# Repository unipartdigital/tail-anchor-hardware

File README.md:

# tail-anchor-hardware

Standalone anchor for tail

See https://github.com/unipartdigital/tail for more details

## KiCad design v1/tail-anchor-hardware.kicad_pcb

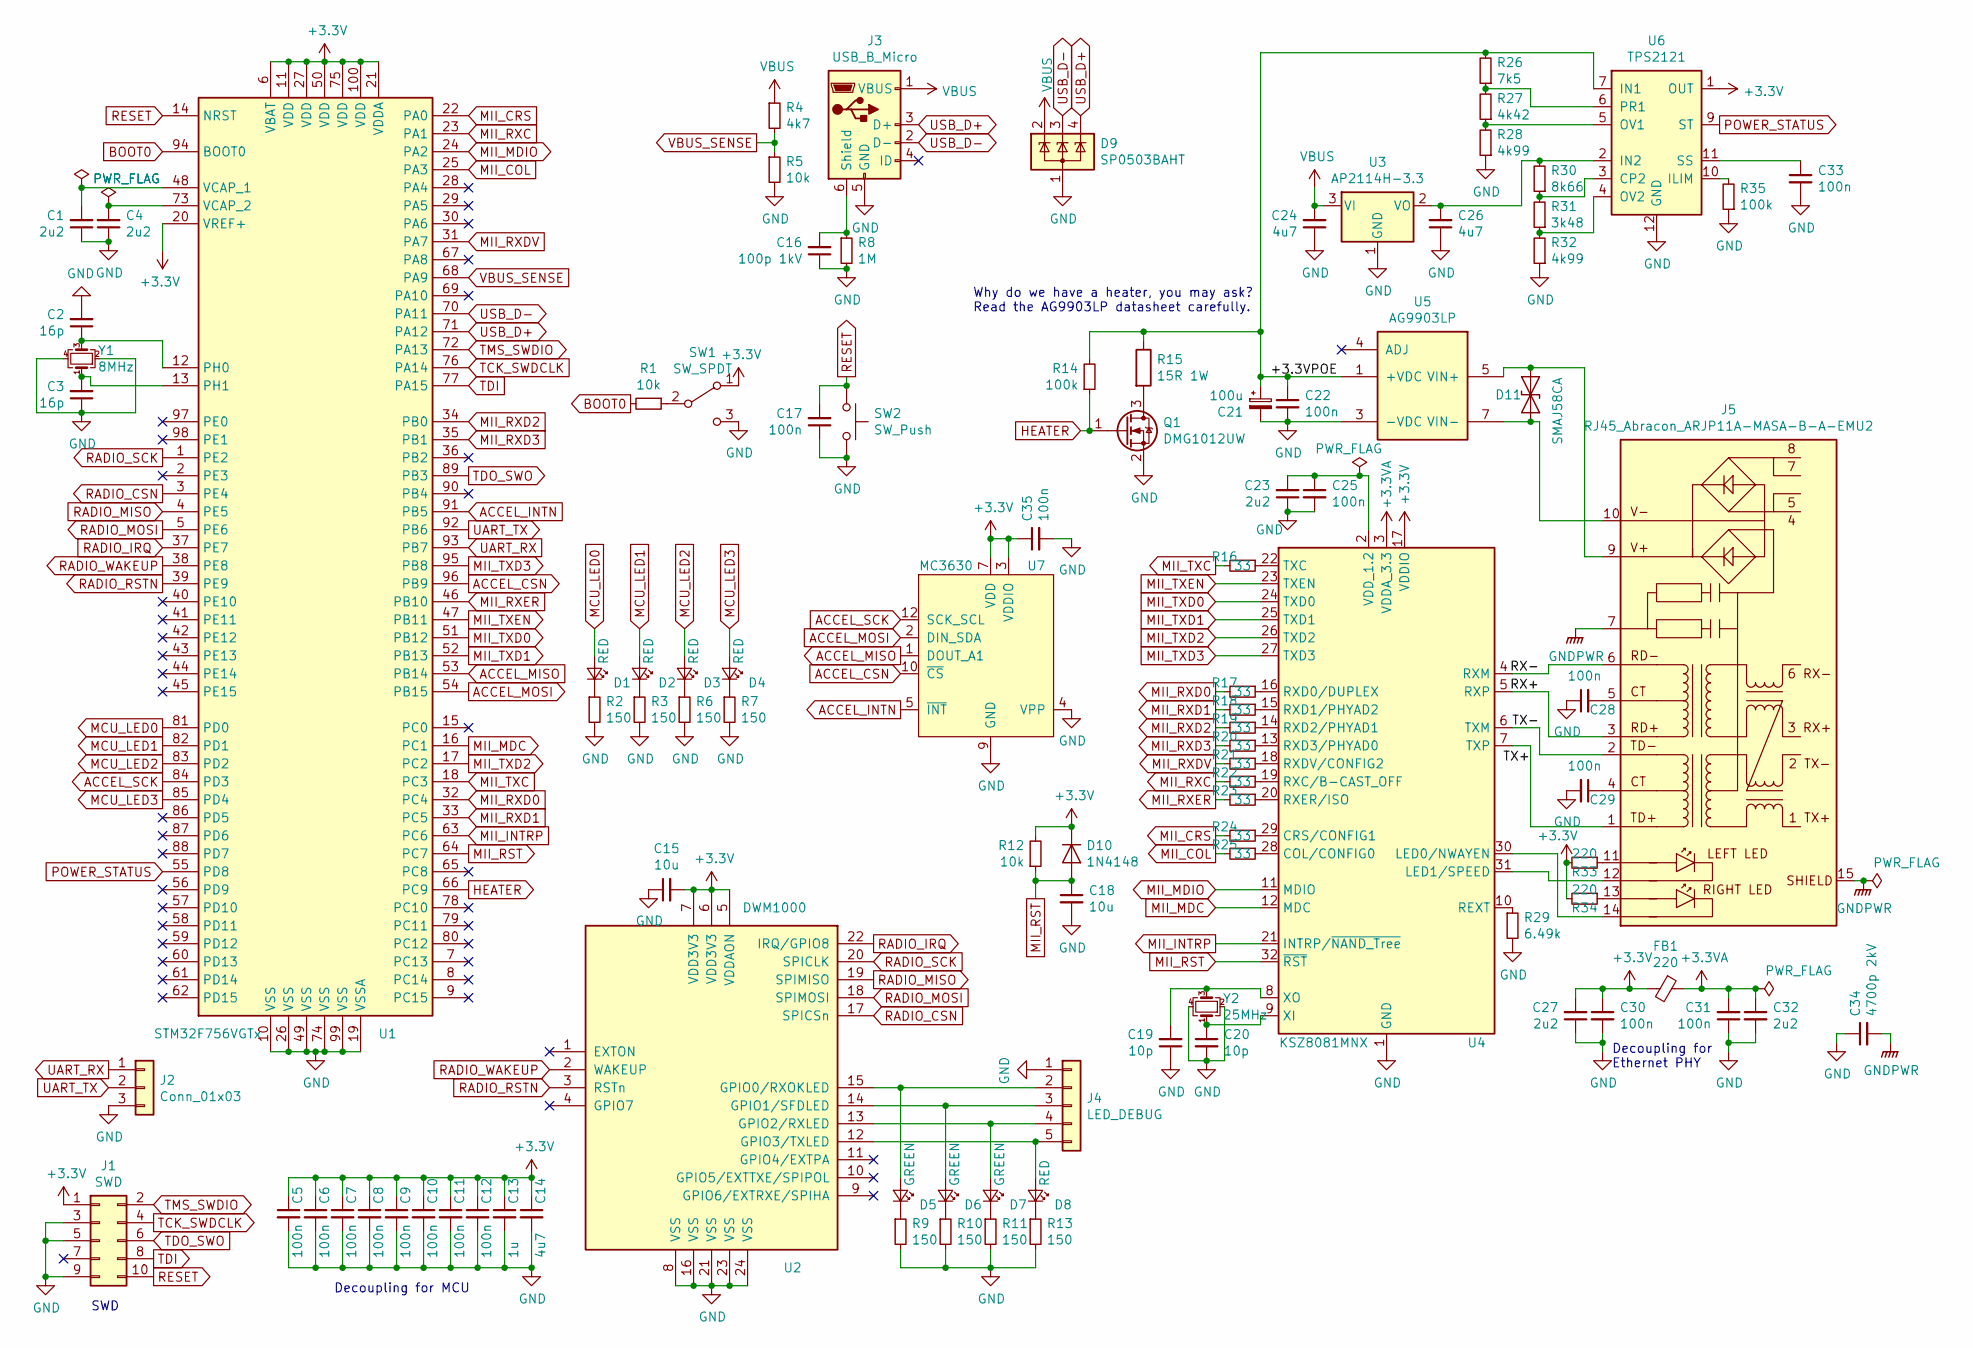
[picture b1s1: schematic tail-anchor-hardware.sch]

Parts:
C1, C4, C23, C27, C32: 2u2; C_0402_1005Metric; MPN GRM155R60J225ME95D
C2, C3: 16p; C_0402_1005Metric; MPN GJM1555C1H160GB01D
C5, C6, C7, C8, C9, C10, C11, C12, C17, C22, C25, C28, C29, C30, C31, C33, C35: 100n; C_0402_1005Metric; MPN MC0402X104K6R3CT
C13: 1u; C_0402_1005Metric; MPN CL05A105KQ5NNNC
C14, C24, C26: 4u7; C_0402_1005Metric; MPN GRM155R60G475ME87D
C15, C18: 10u; C_0402_1005Metric; MPN GRM155R60J106ME44D
C16: 100p 1kV; C_1206_3216Metric; MPN C1206C101JDGACAUTO
C19, C20: 10p; C_0402_1005Metric; MPN MCMT15N100F100CT
C21: 100u; C_Elec_5x5.8; MPN VZT101M1CTR-0506
C34: 4700p 2kV; C_1812_4532Metric; MPN C1812C472KGRACTU
D1, D2, D3, D4, D8: RED; LED_0603_1608Metric; MPN KP-1608SURCK
D5, D6, D7: GREEN; LED_0603_1608Metric; MPN KP-1608CGCK
D9: SP0503BAHT; SOT-143; MPN SP0503BAHTG
D10: 1N4148; D_SOD-123; MPN 1N4148W+
D11: SMAJ58CA; D_SMA; MPN SMAJ58CA
FB1: 220; L_0402_1005Metric; MPN BLM15AG221SN1D
J1: SWD; PinHeader_2x05_P1.27mm_Vertical_SMD; MPN FTSH-105-01-L-DV
J2: Conn_01x03; PinHeader_1x03_P2.54mm_Horizontal; MPN MC34747
J3: USB_B_Micro; USB_Micro-B_Molex_47346-0001; MPN 47346-0001
J4: LED_DEBUG; PinHeader_1x05_P2.54mm_Vertical; MPN 2211S-05G
J5: RJ45_Abracon_ARJP11A-MASA-B-A-EMU2; RJ45_Abracon_ARJP11A-MA_Horizontal; MPN ARJP11A-MASA-B-A-EMU2
Q1: DMG1012UW; SOT-323_SC-70; MPN DMG1012UW
R1, R5, R12: 10k; R_0402_1005Metric; MPN MCWR04X1002FTL
R2, R3, R6, R7, R9, R10, R11, R13: 150; R_0402_1005Metric; MPN MCWR04X1500FTL
R4: 4k7; R_0402_1005Metric; MPN MCWR04X4701FTL
R8: 1M; R_2010_5025Metric; MPN MCHVR0AJTEU1004
R14, R35: 100k; R_0402_1005Metric; MPN MCWR04X1003FTL
R15: 15R 1W; R_MELF_MMB-0207; MPN SMA-A0207FTDT15R
R16, R17, R18, R19, R20, R21, R22, R23, R24, R25: 33; R_0402_1005Metric; MPN CRG0402F33R
R26: 7k5; R_0402_1005Metric; MPN MCWR04X7501FTL
R27: 4k42; R_0402_1005Metric; MPN MCMR04X4421FTL
R28, R32: 4k99; R_0402_1005Metric; MPN MCWR04X4991FTL
R29: 6.49k; R_0402_1005Metric; MPN MCWR04X6491FTL
R30: 8k66; R_0402_1005Metric; MPN MCWR04X8661FTL
R31: 3k48; R_0402_1005Metric; MPN MC00625W040213K48
R33, R34: 220; R_0402_1005Metric; MPN MCWR04X2200FTL
SW1: SW_SPDT; SW_Slide_1P2T_CK_OS102011MS2Q; MPN OS102011MA1QN1C
SW2: SW_Push; SW_Tactile_SPST_Angled_PTS645Vx58-2LFS; MPN 1825027-8
U1: STM32F756VGTx; LQFP-100_14x14mm_P0.5mm; MPN STM32F756VGT6
U2: DWM1000; MPN DWM1000
U3: AP2114H-3.3; SOT-223-3_TabPin2; MPN AP2114H-3.3TRG1
U4: KSZ8081MNX; QFN-32-1EP_5x5mm_P0.5mm_EP3.45x3.45mm; MPN KSZ8081MNXIA
U5: AG9903LP; AG9900LP; MPN Ag9903LP
U6: TPS2121; Texas_VQFN-HR-12_2x2.5mm_P0.5mm; MPN TPS2121RUXR
U7: MC3630; LGA-12_2x2mm_P0.5mm; MPN MC3630
Y1: 8MHz; Crystal_SMD_5032-4Pin_5.0x3.2mm; MPN MCSJK-7I-8.00-18-10-60-B-10
Y2: 25MHz; Crystal_SMD_3225-4Pin_3.2x2.5mm; MPN MCSJK-7U-25.00-10-30-60-B-30

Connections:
+3.3VA: C31.2, C32.1, FB1.1, U4.3 (VDDA_3.3)
+3V3: C5.1, C6.1, C7.1, C8.1, C9.1, C10.1, C11.1, C12.1, C13.1, C14.1, C15.2, C27.2, C30.1, C35.1, D10.1 (K), FB1.2, J1.1, R12.2, R33.2, R34.2, SW1.1 (A), U1.6 (VBAT), U1.11 (VDD), U1.20 (VREF+), U1.21 (VDDA), U1.27 (VDD), U1.50 (VDD), U1.75 (VDD), U1.100 (VDD), U2.5 (VDDAON), U2.6 (VDD3V3), U2.7 (VDD3V3), U4.17 (VDDIO), U6.1 (OUT), U6.8 (OUT), U7.3 (VDDIO), U7.7 (VDD)
/+3.3VPOE: C21.1, C22.1, R14.2, R15.1, R26.2, U5.1 (+VDC), U5.2 (+VDC), U6.7 (IN1)
/RX+: J5.3 (RD+), U4.5 (RXP)
/RX-: J5.6 (RD-), U4.4 (RXM)
/TX+: J5.1 (TD+), U4.7 (TXP)
/TX-: J5.2 (TD-), U4.6 (TXM)
ACCEL_CSN: U1.96 (PB9), U7.10 (~CS)
ACCEL_INTN: U1.91 (PB5), U7.5 (~INT)
ACCEL_MISO: U1.53 (PB14), U7.1 (DOUT_A1)
ACCEL_MOSI: U1.54 (PB15), U7.2 (DIN_SDA)
ACCEL_SCK: U1.84 (PD3), U7.12 (SCK_SCL)
BOOT0: R1.2, U1.94 (BOOT0)
GND: C1.1, C2.2, C3.1, C4.1, C5.2, C6.2, C7.2, C8.2, C9.2, C10.2, C11.2, C12.2, C13.2, C14.2, C15.1, C16.1, C17.1, C18.2, C19.1, C20.2, C21.2, C22.2, C23.1, C24.1, C25.2, C26.1, C27.1, C28.1, C29.2, C30.2, C31.1, C32.2, C33.2, C34.1, C35.2, D9.1 (A), J1.3, J1.5, J1.9, J2.3, J3.5 (GND), J4.1, Q1.2 (S), R2.2, R3.2, R5.2, R6.2, R7.2, R8.2, R9.2, R10.2, R11.2, R13.2, R28.1, R29.2, R32.1, R35.1, SW1.3 (C), SW2.2, U1.10 (VSS), U1.19 (VSSA), U1.26 (VSS), U1.49 (VSS), U1.74 (VSS), U1.99 (VSS), U2.8 (VSS), U2.16 (VSS), U2.21 (VSS), U2.23 (VSS), U2.24 (VSS), U3.1 (GND), U4.1 (GND), U4.33 (GND), U5.3 (-VDC), U6.12 (GND), U7.4 (VPP), U7.9 (GND), Y1.2, Y1.4, Y2.2, Y2.4
GNDPWR: C34.2, J5.7, J5.15 (SHIELD)
HEATER: Q1.1 (G), R14.1, U1.66 (PC9)
MCU_LED0: D1.2 (A), U1.81 (PD0)
MCU_LED1: D2.2 (A), U1.82 (PD1)
MCU_LED2: D3.2 (A), U1.83 (PD2)
MCU_LED3: D4.2 (A), U1.85 (PD4)
MII_COL: R25.2, U1.25 (PA3)
MII_CRS: R24.2, U1.22 (PA0)
MII_INTRP: U1.63 (PC6), U4.21 (INTRP/~NAND_Tree)
MII_MDC: U1.16 (PC1), U4.12 (MDC)
MII_MDIO: U1.24 (PA2), U4.11 (MDIO)
MII_RST: C18.1, D10.2 (A), R12.1, U1.64 (PC7), U4.32 (~RST)
MII_RXC: R22.2, U1.23 (PA1)
MII_RXD0: R17.2, U1.32 (PC4)
MII_RXD1: R18.2, U1.33 (PC5)
MII_RXD2: R19.2, U1.34 (PB0)
MII_RXD3: R20.2, U1.35 (PB1)
MII_RXDV: R21.2, U1.31 (PA7)
MII_RXER: R23.2, U1.46 (PB10)
MII_TXC: R16.2, U1.18 (PC3)
MII_TXD0: U1.51 (PB12), U4.24 (TXD0)
MII_TXD1: U1.52 (PB13), U4.25 (TXD1)
MII_TXD2: U1.17 (PC2), U4.26 (TXD2)
MII_TXD3: U1.95 (PB8), U4.27 (TXD3)
MII_TXEN: U1.47 (PB11), U4.23 (TXEN)
unnamed: C1.2, U1.48 (VCAP_1)
unnamed: C2.1, U1.12 (PH0), Y1.3
unnamed: C3.2, U1.13 (PH1), Y1.1
unnamed: C4.2, U1.73 (VCAP_2)
unnamed: C16.2, J3.6 (Shield), R8.1
unnamed: C19.2, U4.8 (XO), Y2.3
unnamed: C20.1, U4.9 (XI), Y2.1
unnamed: C23.2, C25.1, U4.2 (VDD_1.2)
unnamed: C26.2, R30.2, U3.2 (VO), U6.2 (IN2)
unnamed: C28.2, J5.5 (CT)
unnamed: C29.1, J5.4 (CT)
unnamed: C33.1, U6.11 (SS)
unnamed: D1.1 (K), R2.1
unnamed: D2.1 (K), R3.1
unnamed: D3.1 (K), R6.1
unnamed: D4.1 (K), R7.1
unnamed: D5.1 (K), R9.1
unnamed: D5.2 (A), J4.2, U2.15 (GPIO0/RXOKLED)
unnamed: D6.1 (K), R10.1
unnamed: D6.2 (A), J4.3, U2.14 (GPIO1/SFDLED)
unnamed: D7.1 (K), R11.1
unnamed: D7.2 (A), J4.4, U2.13 (GPIO2/RXLED)
unnamed: D8.1 (K), R13.1
unnamed: D8.2 (A), J4.5, U2.12 (GPIO3/TXLED)
unnamed: D11.1 (A1), J5.9 (V+), U5.5 (VIN+), U5.6 (VIN+)
unnamed: D11.2 (A2), J5.10 (V-), U5.7 (VIN-), U5.8 (VIN-)
unnamed: J5.11 (LLED+), R33.1
unnamed: J5.12 (LLED-), U4.31 (LED1/SPEED)
unnamed: J5.13 (RLED+), R34.1
unnamed: J5.14 (RLED-), U4.30 (LED0/NWAYEN)
unnamed: Q1.3 (D), R15.2
unnamed: R1.1, SW1.2 (B)
unnamed: R16.1, U4.22 (TXC)
unnamed: R17.1, U4.16 (RXD0/DUPLEX)
unnamed: R18.1, U4.15 (RXD1/PHYAD2)
unnamed: R19.1, U4.14 (RXD2/PHYAD1)
unnamed: R20.1, U4.13 (RXD3/PHYAD0)
unnamed: R21.1, U4.18 (RXDV/CONFIG2)
unnamed: R22.1, U4.19 (RXC/B-CAST_OFF)
unnamed: R23.1, U4.20 (RXER/ISO)
unnamed: R24.1, U4.29 (CRS/CONFIG1)
unnamed: R25.1, U4.28 (COL/CONFIG0)
unnamed: R26.1, R27.2, U6.6 (PR1)
unnamed: R27.1, R28.2, U6.5 (OV1)
unnamed: R29.1, U4.10 (REXT)
unnamed: R30.1, R31.2, U6.3 (CP2)
unnamed: R31.1, R32.2, U6.4 (OV2)
unnamed: R35.2, U6.10 (ILIM)
POWER_STATUS: U1.55 (PD8), U6.9 (ST)
RADIO_CSN: U1.3 (PE4), U2.17 (SPICSn)
RADIO_IRQ: U1.37 (PE7), U2.22 (IRQ/GPIO8)
RADIO_MISO: U1.4 (PE5), U2.19 (SPIMISO)
RADIO_MOSI: U1.5 (PE6), U2.18 (SPIMOSI)
RADIO_RSTN: U1.39 (PE9), U2.3 (RSTn)
RADIO_SCK: U1.1 (PE2), U2.20 (SPICLK)
RADIO_WAKEUP: U1.38 (PE8), U2.2 (WAKEUP)
RESET: C17.2, J1.10, SW2.1, U1.14 (NRST)
TCK_SWDCLK: J1.4, U1.76 (PA14)
TDI: J1.8, U1.77 (PA15)
TDO_SWO: J1.6, U1.89 (PB3)
TMS_SWDIO: J1.2, U1.72 (PA13)
UART_RX: J2.1, U1.93 (PB7)
UART_TX: J2.2, U1.92 (PB6)
USB_D+: D9.4 (K), J3.3 (D+), U1.71 (PA12)
USB_D-: D9.3 (K), J3.2 (D-), U1.70 (PA11)
VBUS: C24.2, D9.2 (K), J3.1 (VBUS), R4.1, U3.3 (VI)
VBUS_SENSE: R4.2, R5.1, U1.68 (PA9)

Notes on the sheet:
SWD
Decoupling for Ethernet PHY
Decoupling for MCU
Why do we have a heater, you may ask? Read the AG9903LP datasheet carefully.

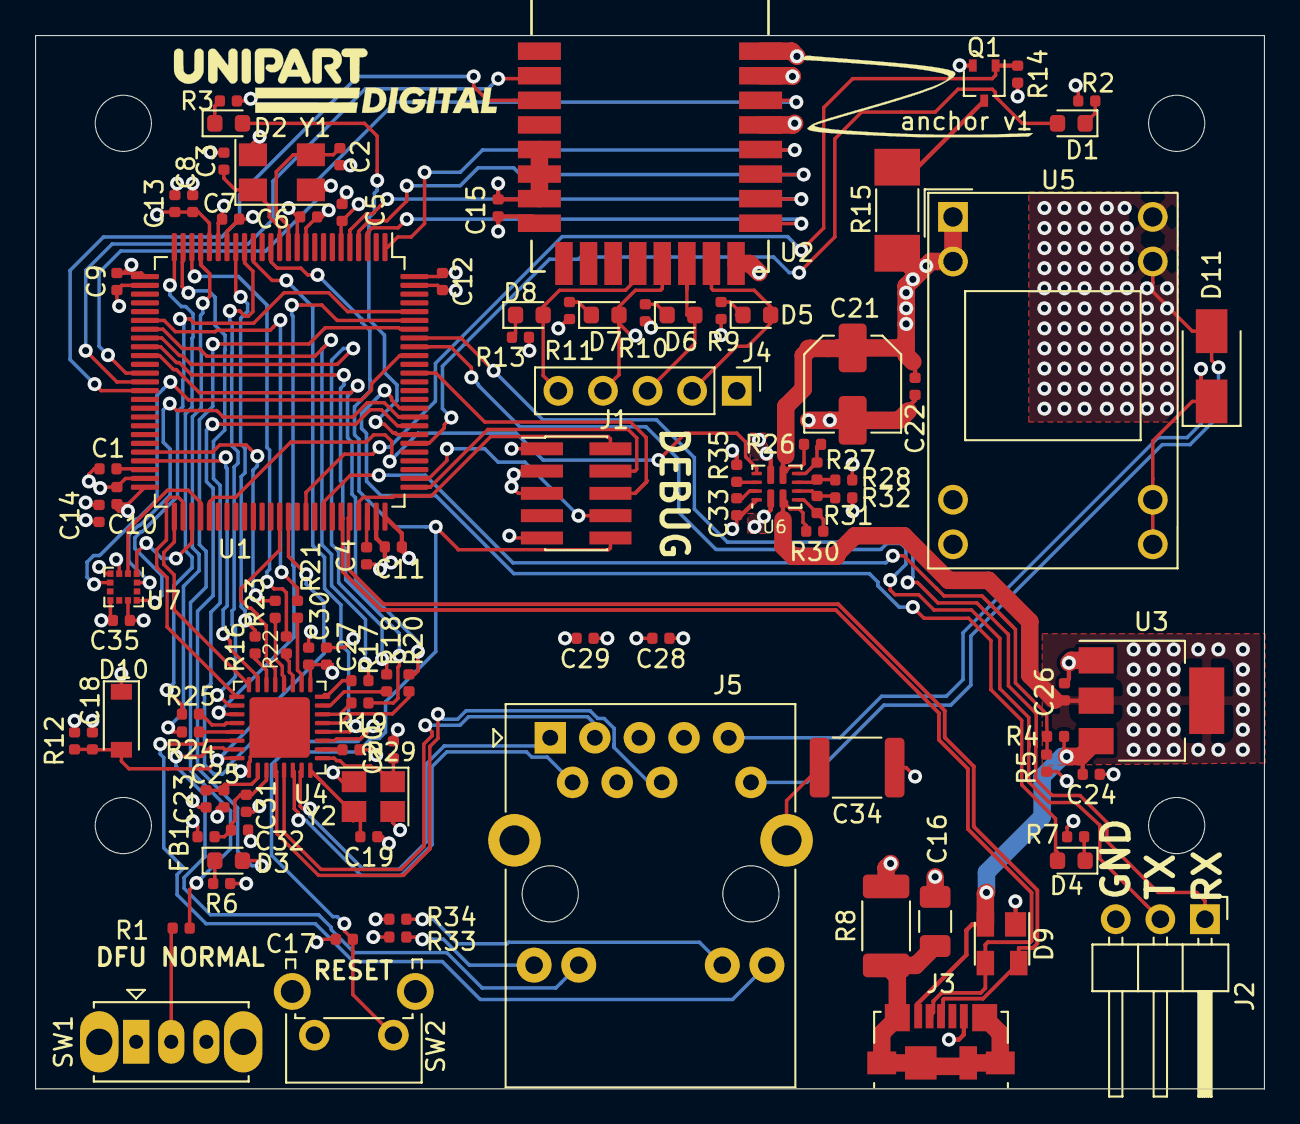
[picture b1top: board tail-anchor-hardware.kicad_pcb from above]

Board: 4 copper layers, 70.0 x 60.0 mm, 99 parts (0 on the bottom side), 106 nets.

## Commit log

2020-07-31 v1: Initial checkin of standalone anchor
2020-07-31 v1: remove extraneous files
2020-07-31 v1: File to append to BOM for manufacturing
    This is necessary because KiCad doesn't yet know how to manage extra BOM
    items for mechanical parts.
    Simply cat this file to the end of the generated csv file before sending
    it off for manufacture.
2021-12-24 Create LICENSE
2021-12-24 Create COPYRIGHT
